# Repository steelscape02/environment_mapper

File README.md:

# Environment Mapper Project

- [Assembly](#assembly)
- [How it works](#how-it-works)

---

**The ability to scan an environment in 3D can take your project to the next dimension.. Literally.**

Unfortunately, prebuilt LiDAR scanning systems are very cost prohibitive for hobbyists and small teams. That's why we 
designed a **3D LiDAR environment mapping system** based on an STM32, TFMini LiDAR, and 2 SG90 mini servos.
This project is designed to be highly portable. Just design a power network as outlined in the `shield` folder, attach the 
noted hardware (see _Assembly_), upload the STM32 project in `firmware` to your own STM32, and viola!
You now have a functional 3D environment mapper.

To make this project more interactive, a desktop app is also included in this repo, designed to be a companion to the 
hardware, translating the points over UART and displaying them in a point cloud right on your computer.
Utilizing the lightweight OpenGL C++ framework, this app can achieve a 100Hz refresh rate and a rotatable model using GLM.

## Assembly

### Components

To build the environment mapper, you will need the following equipment:

- STM32 Nucleo L476RG Development Board (or equivalent)
- 2 SG90 mini servos
- 1 TFMini v2 LiDAR
- 1 pan/tilt mount (this [adafruit mount](https://www.adafruit.com/product/1967#:~:text=Technical%20Details.%20Dimensions%3A%20*%20Base%3A%2037mm%20x,36mm%20%2F%201.5%22x%201.4%22%20*%20Weight%3A%2037g) is a good option)

For the power network and connections, you can either get the equipment below or fabricate a shield using the files in the `shield` directory:

- 1 breadboard
- 5V 3A power supply, and breadboard connector
- jumper cables

### Optional Components

To improve the power distribution to the servos and LiDAR, we included bulk and local decoupling capacitors.
If you want to include these capacitors:

- 3 1uF _ceramic_ capacitors (faster transient response)
- 1 100uF _electrolytic_ capacitor (bigger bulk storage)

### Putting it all together

To assemble the Environment Mapper pan-tilt mount and lidar circuit, reference the schematic below.

<!-- markdownlint-disable MD033 -->
<figure>
  
  <figcaption>Figure 1: Power and UART connections between the MCU and sensor circuitry.</figcaption>
</figure>
<!-- markdownlint-enable MD033 -->

<!-- For quick reference, the connections (excluding power and GND) are as follows:

- **LiDAR TX** >  -->

Note that the capacitors are optional. However, it is recommended that an external 5V supply is used to power the 5V rail,
rather than the STM32's rail, due to the high current demands of the 2 SG90 servos during startup. This can be provided by
connecting a suitable power supply (for breadboarding
[this supply](https://www.amazon.com/dp/B0CWFG5LBM?lv=shuf&hvlocphy=106466&linkCode=df0&psc=1&hvnetw=o&hvadid=80195839596071&hvbmt=be&hvlocint=&hvdev=c&hvocijid=17449357714194124364-B0CWFG5LBM-&hvqmt=e&hvexpln=0&tag=bingshoppinga-20&hvtargid=pla-4583795320013176&channelId=69&ref_=asc_df_B0CWFG5LBM&plpRedirect=mhFallback)
is a good option) to the E5V port on the STM32, or simply using it as the 5V rail.

## How it works

### Hardware

Now that we've covered the assembly of the environment, a short description of its functionality would be in order.
To begin with the hardware, we used 2 SG90 servos and a Benewake TFMini V2 LiDAR sensor to provide the sensor circuit.
The servos are controlled with PWM, while the LiDAR is controlled using a UART connection.
For more information on the controls of either component, please take a look at
[the code](https://github.com/steelscape02/environment_mapper/tree/main/STM32Project/EnviornmentMapper)
in the repo.

<!-- Include Hardware Block Diagram -->

### Software

As the pan-tilt mount rotates during operation, the PWM data sent to the servos and the UART data received
from the LiDAR are assembled on the STM32 board into a UART packet, the structure of which is shown in **Figure 2**,
for display.

<!-- markdownlint-disable MD033 -->
<figure>
  
  <figcaption>Figure 2: Environment Mapper UART Packet Structure</figcaption>
</figure>
<!-- markdownlint-enable MD033 -->

This 13-byte packet contains all of the information needed to display the points and provide some feedback on reading
accuracy. Please refer to the table below for what each byte does:

| Byte      |   Type          |                      Description                                                      |
|-----------|-----------------|---------------------------------------------------------------------------------------|
| 0x59 (x2) | Sync Bytes      | Helps the program determine the start of a new packet.                                |
| LEN       | Length          | Tells the program how long of a packet to expect                                      |
| DIST_H+L  | Distance        | 2-byte distance recorded in LiDAR, in cm                                              |
| STR_H+L   | Signal Strength | Signal strength in LiDAR, helping to determine reflectivity of the detected object    |
| PAN_H+L   | Pan Angle       | Pan angle, recorded from the PWM signals sent to the pan servo                        |
| TILT_H+L  | Tilt Angle      | Tilt angle, recorded from PWM signals sent to the tilt servo                          |
| CRC_H+L   | CRC-16 Checksum | CRC checksum for the payload. Provides excellent protection against packet corruption |

Once the desktop program has received a packet over UART, it translates the received point into a polar coordinate system,
using an `(elevation, azimuth, distance)` system. These points are loaded into a LIFO queue, which is then read on a different thread by the graphics utility, which updates the points in near-realtime.

## Citations

If you use this project or Open3D, please cite:

```bibtex
@article{Zhou2018,
  author = {Qian-Yi Zhou and Jaesik Park and Vladlen Koltun},
  title = {{Open3D}: {A} Modern Library for {3D} Data Processing},
  journal = {arXiv:1801.09847},
  year = {2018},
}
```

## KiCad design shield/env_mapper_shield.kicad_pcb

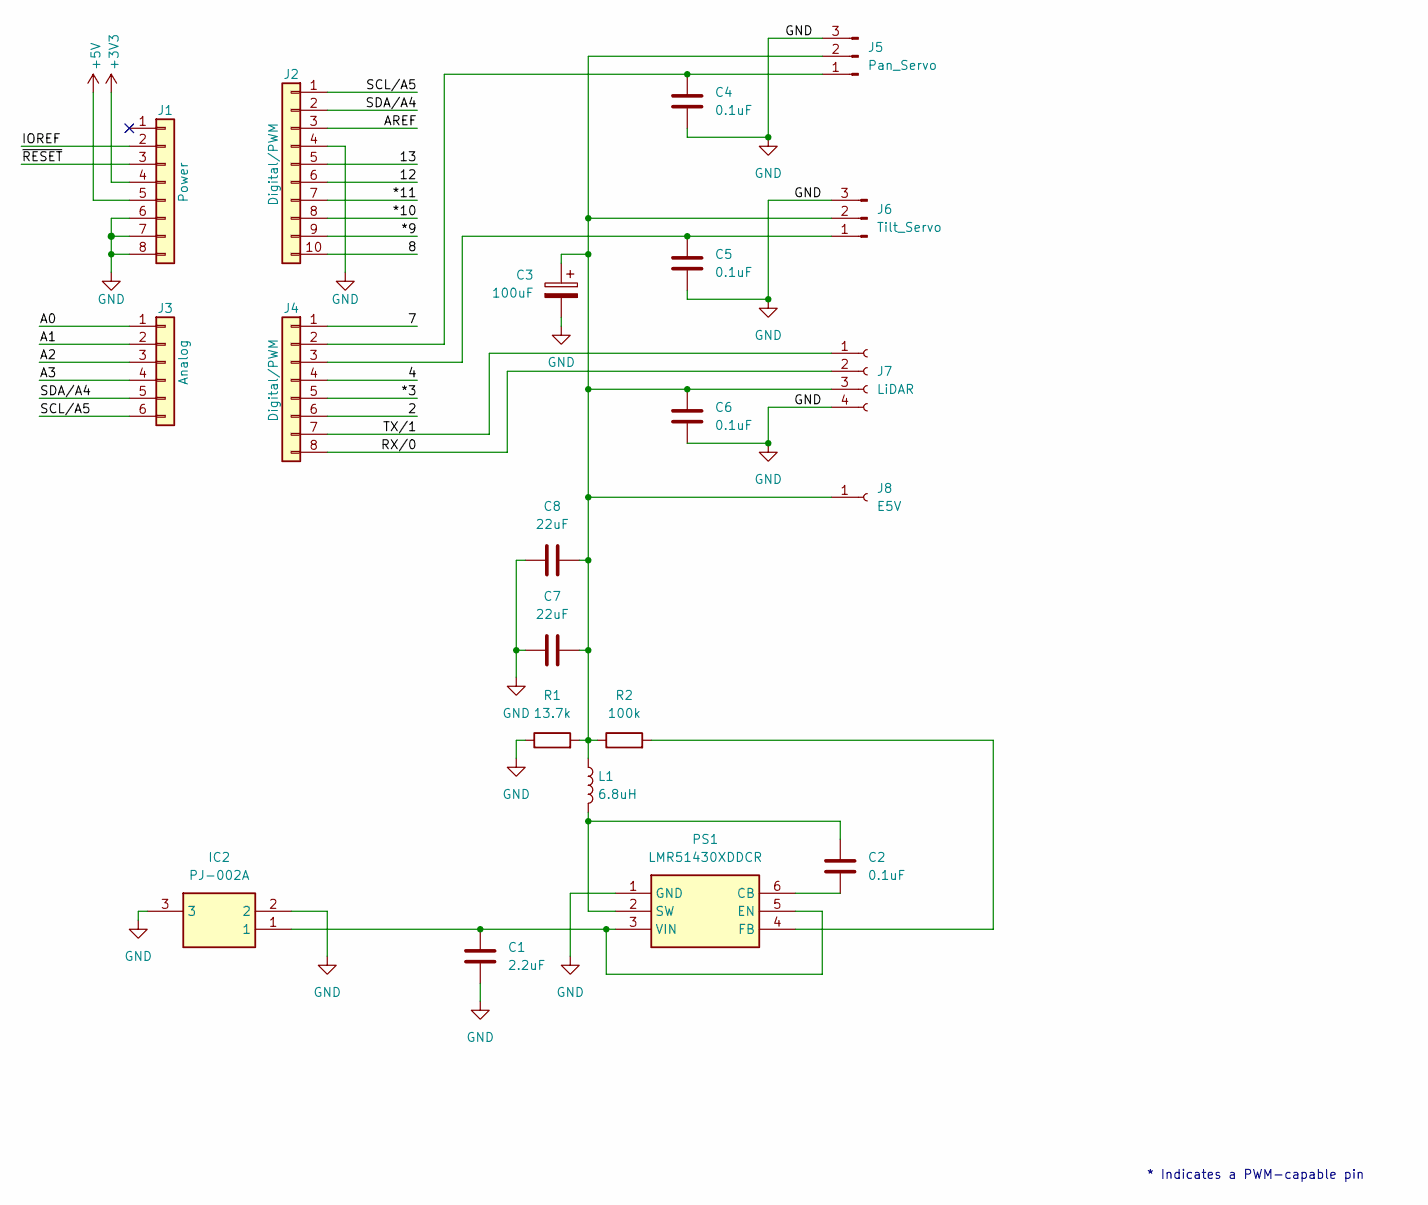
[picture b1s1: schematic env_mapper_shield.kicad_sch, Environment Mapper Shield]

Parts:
C1: 2.2uF; R_0402_1005Metric_Pad0.72x0.64mm_HandSolder
C2, C4, C5, C6: 0.1uF; R_0402_1005Metric_Pad0.72x0.64mm_HandSolder
C3: 100uF; CP_Radial_D8.0mm_P3.50mm
C7, C8: 22uF; C_0805_2012Metric_Pad1.18x1.45mm_HandSolder
IC2: PJ-002A; PJ002A; Manufacturer_Part_Number PJ-002A; Mouser Part Number 490-PJ-002A
J1: Power; PinSocket_1x08_P2.54mm_Vertical
J2: Digital/PWM; PinSocket_1x10_P2.54mm_Vertical
J3: Analog; PinSocket_1x06_P2.54mm_Vertical
J4: Digital/PWM; PinSocket_1x08_P2.54mm_Vertical
J5: Pan_Servo; PinHeader_1x03_P2.54mm_Vertical
J6: Tilt_Servo; PinHeader_1x03_P2.54mm_Vertical
J7: LiDAR; PinSocket_1x04_P2.54mm_Vertical
J8: E5V; PinHeader_1x01_P2.54mm_Vertical
L1: 6.8uH; ETQ-P3M_KVP
PS1: LMR51430XDDCR; SOT95P280X110-6N; Manufacturer_Part_Number LMR51430XDDCR; Mouser Part Number 595-LMR51430XDDCR
R1: 13.7k; R_0402_1005Metric_Pad0.72x0.64mm_HandSolder
R2: 100k; R_0402_1005Metric_Pad0.72x0.64mm_HandSolder

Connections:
+3V3: J1.4
+5V: J1.5
/2: J4.6
/4: J4.4
/7: J4.1
/8: J2.10
/12: J2.6
/13: J2.5
/*3: J4.5
/*9: J2.9
/*10: J2.8
/*11: J2.7
/A0: J3.1
/A1: J3.2
/A2: J3.3
/A3: J3.4
/AREF: J2.3
/IOREF: J1.2
/RX/0: J4.8, J7.2
/SCL/A5: J2.1, J3.6
/SDA/A4: J2.2, J3.5
/TX/1: J4.7, J7.1
/~RESET: J1.3
GND: C1.2, C3.2, C4.2, C5.2, C6.2, C7.1, C8.1, IC2.2, IC2.3, J1.6, J1.7, J1.8, J2.4, J5.3, J6.3, J7.4, PS1.1 (GND), R1.1
unnamed: C4.1, J4.2, J5.1
unnamed: C5.1, J4.3, J6.1
unnamed: C3.1, C6.1, C7.2, C8.2, J5.2, J6.2, J7.3, J8.1 (Pin_1_1), L1.1, R1.2, R2.1
unnamed: C2.2, PS1.6 (CB)
unnamed: C1.1, IC2.1, PS1.3 (VIN), PS1.5 (EN)
unnamed: PS1.4 (FB), R2.2
unnamed: C2.1, L1.2, PS1.2 (SW)

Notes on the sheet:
* Indicates a PWM-capable pin

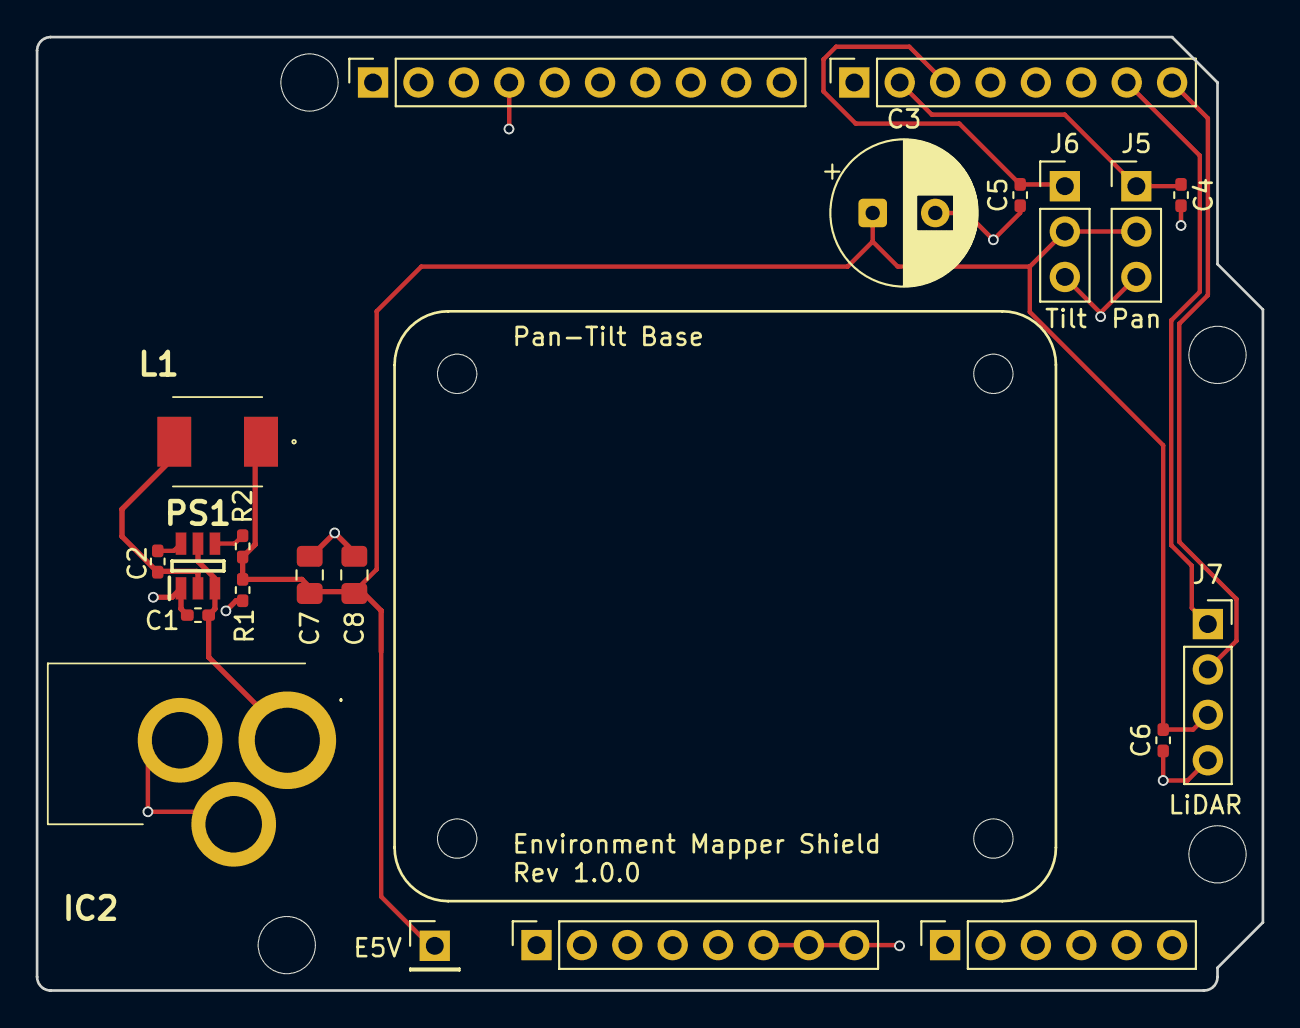
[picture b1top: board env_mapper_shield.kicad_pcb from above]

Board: 2 copper layers, 68.6 x 53.3 mm, 29 parts (0 on the bottom side), 12 nets.

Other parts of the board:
MH1, MH2, MH3, MH4: MountingHole_3.2mm
MNT1, MNT1#2, MNT1#3, MNT1#4: MountingHole_2.2mm_M2
